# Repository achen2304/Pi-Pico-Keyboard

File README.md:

# Pi-Pico-Keyboard
My first project using the pi pico. It's a 22 key keyboard powered by a pi pico which is programmed through python.

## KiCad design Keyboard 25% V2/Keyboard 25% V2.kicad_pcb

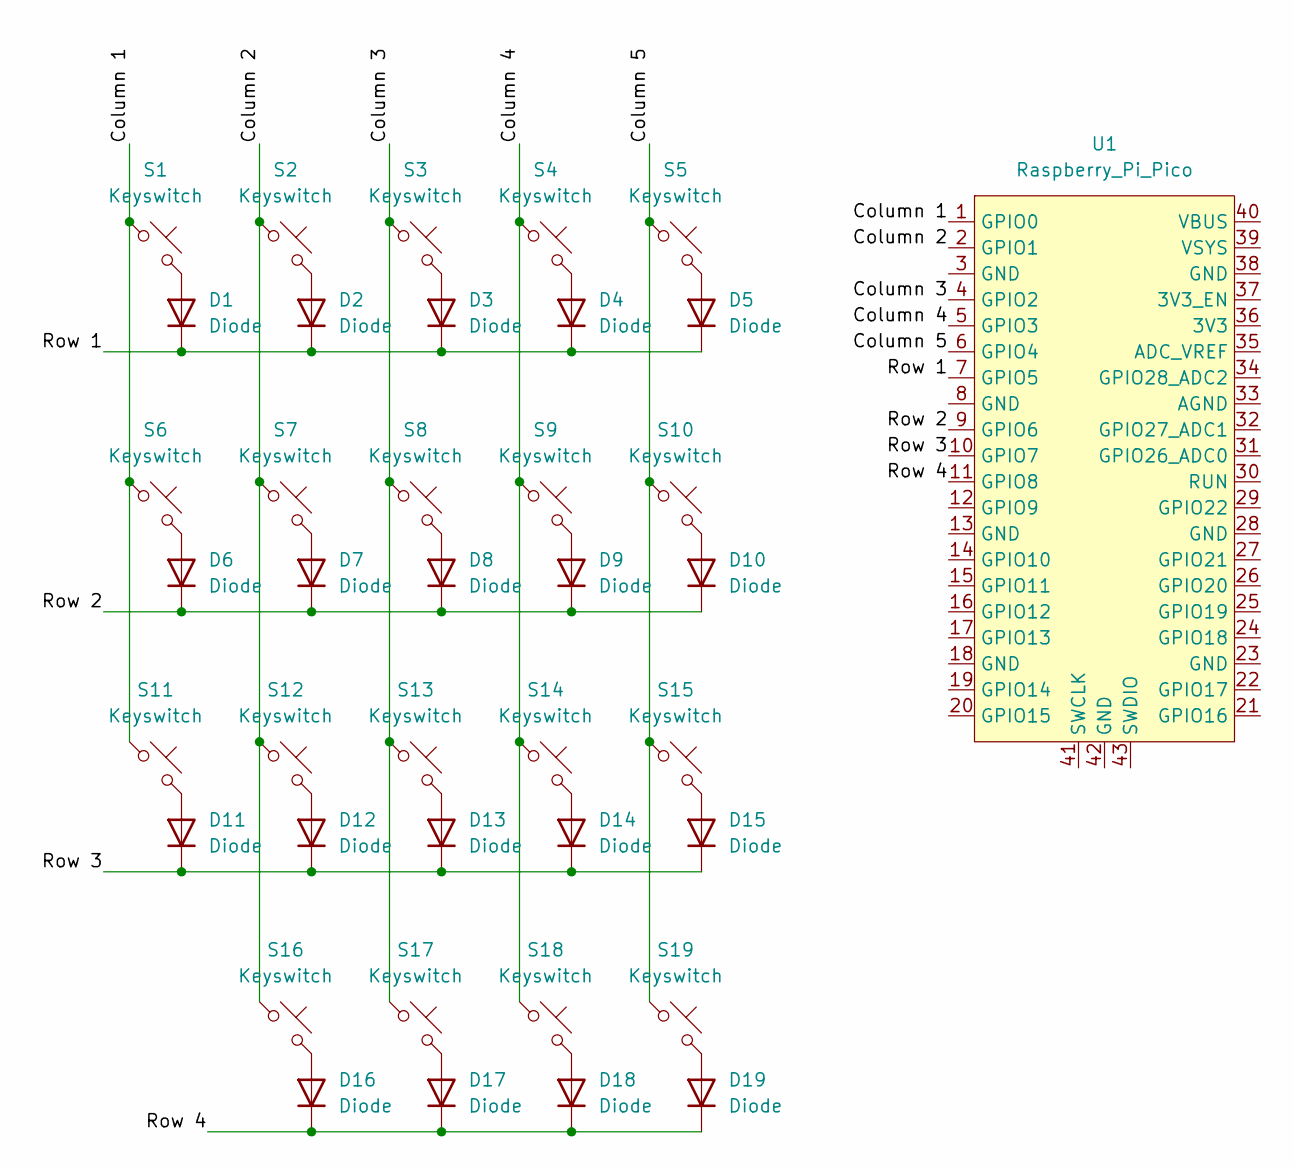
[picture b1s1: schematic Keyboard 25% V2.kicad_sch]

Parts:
D1, D2, D3, D4, D5, D6, D7, D8, D9, D10, D11, D12, D13, D14, D15, D16, D17, D18, D19: Diode; Diode_DO-35
S1, S2, S3, S4, S5, S6, S7, S8, S9, S10, S11, S12, S13, S14, S15, S16, S17, S18, S19: Keyswitch; MX_PCB_1.00u
U1: Raspberry_Pi_Pico

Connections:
/Column 1: S1.1, S6.1, S11.1, U1.1 (GPIO0)
/Column 2: S2.1, S7.1, S12.1, S16.1, U1.2 (GPIO1)
/Column 3: S3.1, S8.1, S13.1, S17.1, U1.4 (GPIO2)
/Column 4: S4.1, S9.1, S14.1, S18.1, U1.5 (GPIO3)
/Column 5: S5.1, S10.1, S15.1, S19.1, U1.6 (GPIO4)
/Row 1: D1.1 (K), D2.1 (K), D3.1 (K), D4.1 (K), D5.1 (K), U1.7 (GPIO5)
/Row 2: D6.1 (K), D7.1 (K), D8.1 (K), D9.1 (K), D10.1 (K), U1.9 (GPIO6)
/Row 3: D11.1 (K), D12.1 (K), D13.1 (K), D14.1 (K), D15.1 (K), U1.10 (GPIO7)
/Row 4: D16.1 (K), D17.1 (K), D18.1 (K), D19.1 (K), U1.11 (GPIO8)
unnamed: D1.2 (A), S1.2
unnamed: D2.2 (A), S2.2
unnamed: D3.2 (A), S3.2
unnamed: D4.2 (A), S4.2
unnamed: D5.2 (A), S5.2
unnamed: D6.2 (A), S6.2
unnamed: D7.2 (A), S7.2
unnamed: D8.2 (A), S8.2
unnamed: D9.2 (A), S9.2
unnamed: D10.2 (A), S10.2
unnamed: D11.2 (A), S11.2
unnamed: D12.2 (A), S12.2
unnamed: D13.2 (A), S13.2
unnamed: D14.2 (A), S14.2
unnamed: D15.2 (A), S15.2
unnamed: D16.2 (A), S16.2
unnamed: D17.2 (A), S17.2
unnamed: D18.2 (A), S18.2
unnamed: D19.2 (A), S19.2

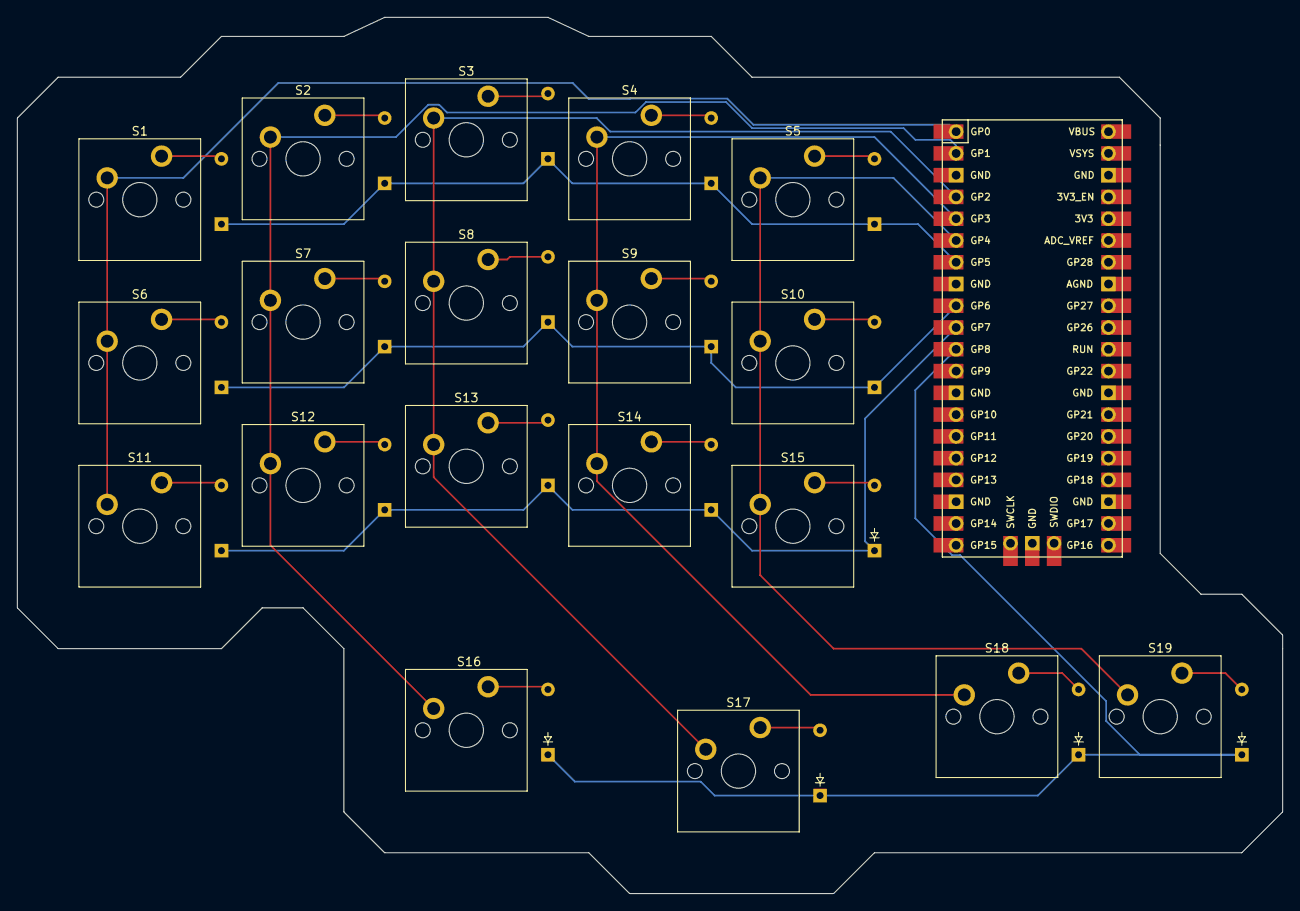
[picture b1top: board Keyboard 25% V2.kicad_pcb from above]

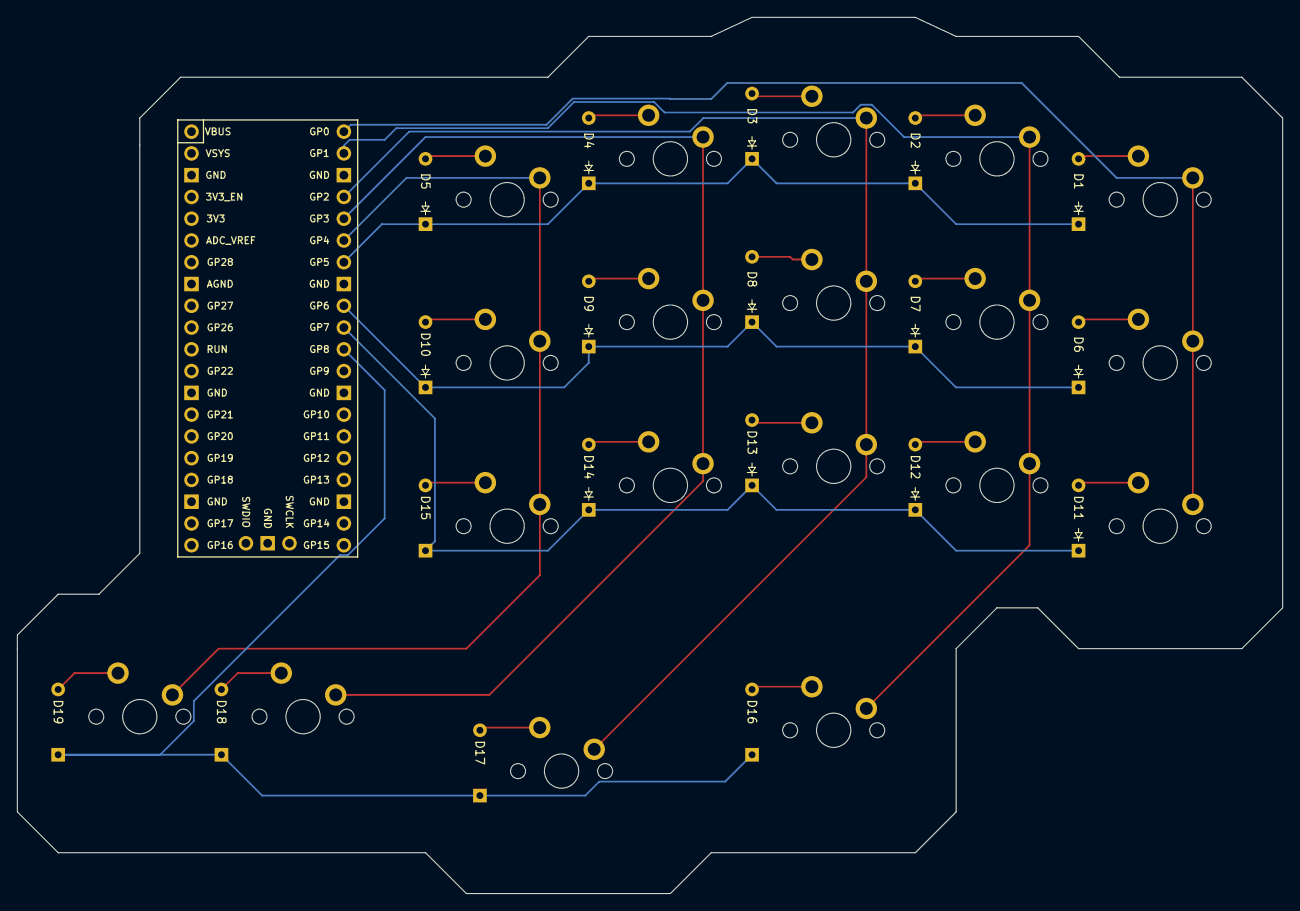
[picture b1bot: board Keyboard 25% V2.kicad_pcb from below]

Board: 2 copper layers, 147.6 x 102.2 mm, 39 parts (14 on the bottom side), 28 nets.
